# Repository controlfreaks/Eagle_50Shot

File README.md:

# Eagle_50Shot
50 shot klunker's EagleCad files

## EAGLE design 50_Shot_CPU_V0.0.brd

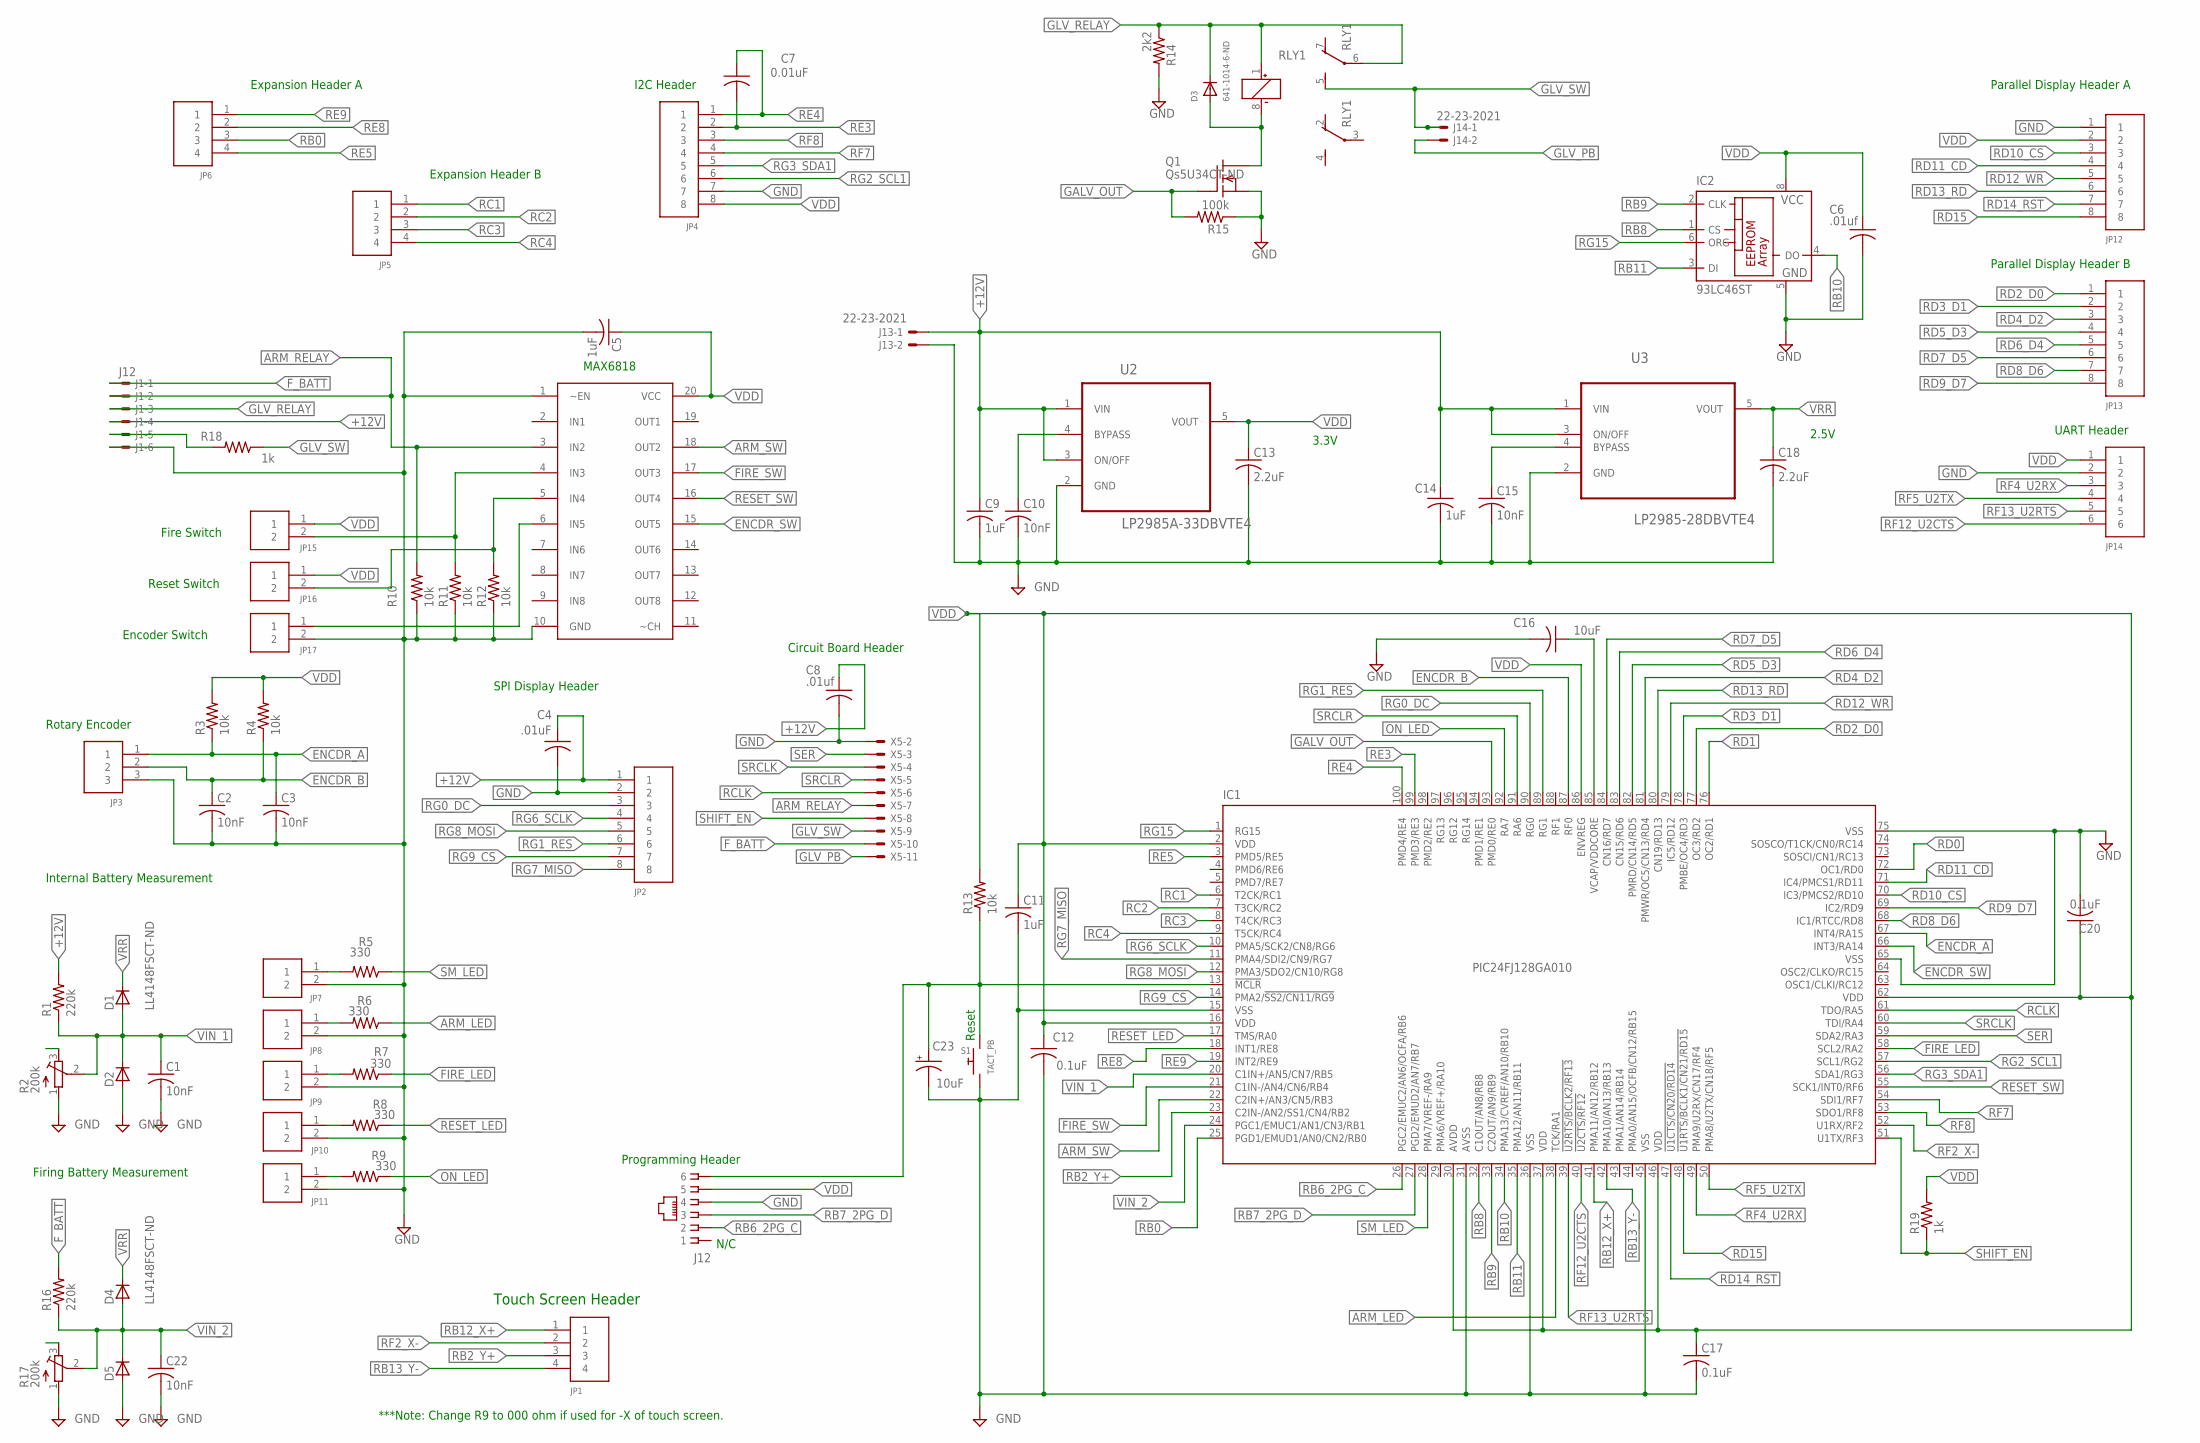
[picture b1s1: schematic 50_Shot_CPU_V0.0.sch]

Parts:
C1, C2, C3, C10, C15, C22: 10nF; C0805
C4: .01uF; C0805
C5, C9, C11, C14: 1uF; C0805
C6, C8: .01uf; C0805
C7: 0.01uF; C0805
C12, C17, C20: 0.1uF; C0805
C13, C18: 2.2uF; C0805
C16: 10uF; C0805
C23: 10uF; CAP3X3
D1, D2, D4, D5: LL4148FSCT-ND; SOD80
D3: 641-1014-6-ND; SOD-123
IC1: PIC24FJ128GA010; TQFP100-14X14
IC2: 93LC46ST; TSSOP8
J1: J12; 22-23-2061
J12: A311422_nd; RJ11-NO_SHIELD
J13, J14: 22-23-2021
JP1, JP5, JP6: SHERLOCK_4PIN_RGT
JP2, JP4, JP12, JP13: SHERLOCK_8PIN_RGT; SHERLOCK_8PIN-RGT
JP3: SHERLOCK_3PIN_RGT
JP7, JP8, JP9, JP10, JP11, JP15, JP16, JP17: SHERLOCK_2PIN_RGT
JP14: SHERLOCK_6PIN_RGT
Q1: Qs5U34CT-ND; SOT23-5L
R1, R16: 220k; M0805
R2, R17: 200k; RTRIM3224X
R3, R4, R10, R11, R12, R13: 10k; M0805
R5, R6, R7, R8, R9: 330; M0805
R14: 2k2; M0805
R15: 100k; M0805
R18, R19: 1k; M0805
RLY1: OMRON; OMRONG6S
S1: TACT_PB; PUSHBUTTON_SMD_SJ
U1: MAX6818; SSOP20
U2: LP2985A-33DBVTE4; SOT95P280X145-5N
U3: LP2985-28DBVTE4; SOT95P280X145-5N
X5: 22-23-2111

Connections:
+12V: C4.1, C8.1, C9.1, C14.1, J1.4, J13.1, JP2.1, R1.2, U2.1 (VIN), U2.3 (ON/OFF), U3.1 (VIN), U3.3 (ON/OFF)
ARM_LED: IC1.38 (TCK/RA1), R6.1
ARM_RELAY: J1.2, R10.2, U1.3 (IN2), X5.7
ARM_SW: IC1.22 (C2IN+/AN3/CN5/RB3), U1.18 (OUT2)
ENCDR_A: C3.1, IC1.67 (INT4/RA15), JP3.1, R3.1
ENCDR_B: C2.1, IC1.87 (RF0), JP3.2, R4.1
ENCDR_SW: IC1.66 (INT3/RA14), U1.15 (OUT5)
FIRE_LED: IC1.58 (SCL2/RA2), R7.1
FIRE_SW: IC1.21 (C1IN-/AN4/CN6/RB4), U1.17 (OUT3)
F_BATT: J1.1, R16.2, X5.10
GALV_OUT: IC1.93 (PMD0/RE0), Q1.1 (G), R15.2
GLV_PB: J14.2, X5.11
GLV_RELAY: D3.C, J1.3, R14.1, RLY1.1 (+), RLY1.6
GLV_SW: J14.1, R18.1, RLY1.5 (S), X5.9
GND: C1.2, C2.2, C3.2, C4.2, C5.2, C6.2, C8.2, C9.2, C10.2, C11.2, C12.2, C13.2, C14.2, C15.2, C16.2, C17.2, C18.2, C20.2, C22.2, C23.-, D2.2 (A), D5.2 (A), IC1.15 (VSS), IC1.31 (AVSS), IC1.36 (VSS), IC1.45 (VSS), IC1.65 (VSS), IC1.75 (VSS), IC2.5 (GND), J1.6, J12.4, J13.2, JP2.2, JP3.3, JP4.7, JP7.2, JP8.2, JP9.2, JP10.2, JP11.2, JP12.1, JP14.2, JP17.2, Q1.2 (S), R2.1 (A), R10.1, R11.1, R12.1, R14.2, R15.1, R17.1 (A), S1.1, S1.2 (1), U1.1 (~EN), U1.10 (GND), U2.2 (GND), U3.2 (GND), X5.2
MCLR: C23.+, IC1.13 (!MCLR), J12.6, R13.1, S1.3 (2), S1.4 (2)
unnamed: D3.A, Q1.5 (D), RLY1.8 (-)
unnamed: JP7.1, R5.2
unnamed: C10.1, U2.4 (BYPASS)
unnamed: C16.1, IC1.85 (VCAP/VDDCORE)
unnamed: JP8.1, R6.2
unnamed: JP17.1, U1.6 (IN5)
unnamed: JP16.2, R12.2, U1.5 (IN4)
unnamed: JP9.1, R7.2
unnamed: J1.5, R18.2
unnamed: JP10.1, R8.2
unnamed: JP11.1, R9.2
unnamed: C15.1, U3.4 (BYPASS)
unnamed: JP15.2, R11.2, U1.4 (IN3)
ON_LED: IC1.92 (RA7), R9.1
RB0: IC1.25 (PGD1/EMUD1/AN0/CN2/RB0), JP6.3
RB2_Y+: IC1.23 (C2IN-/AN2/SS1/CN4/RB2), JP1.3
RB6_2PG_C: IC1.26 (PGC2/EMUC2/AN6/OCFA/RB6), J12.2
RB7_2PG_D: IC1.27 (PGD2/EMUD2/AN7/RB7), J12.3
RB8: IC1.32 (C1OUT/AN8/RB8), IC2.1 (CS)
RB9: IC1.33 (C2OUT/AN9/RB9), IC2.2 (CLK)
RB10: IC1.34 (PMA13/CVREF/AN10/RB10), IC2.4 (DO)
RB11: IC1.35 (PMA12/AN11/RB11), IC2.3 (DI)
RB12_X+: IC1.41 (PMA11/AN12/RB12), JP1.1
RB13_Y-: IC1.42 (PMA10/AN13/RB13), JP1.4
RC1: IC1.6 (T2CK/RC1), JP5.1
RC2: IC1.7 (T3CK/RC2), JP5.2
RC3: IC1.8 (T4CK/RC3), JP5.3
RC4: IC1.9 (T5CK/RC4), JP5.4
RCLK: IC1.61 (TDO/RA5), X5.6
RD0: IC1.72 (OC1/RD0)
RD1: IC1.76 (OC2/RD1)
RD2_D0: IC1.77 (OC3/RD2), JP13.1
RD3_D1: IC1.78 (PMBE/OC4/RD3), JP13.2
RD4_D2: IC1.81 (PMWR/OC5/CN13/RD4), JP13.3
RD5_D3: IC1.82 (PMRD/CN14/RD5), JP13.4
RD6_D4: IC1.83 (CN15/RD6), JP13.5
RD7_D5: IC1.84 (CN16/RD7), JP13.6
RD8_D6: IC1.68 (IC1/RTCC/RD8), JP13.7
RD9_D7: IC1.69 (IC2/RD9), JP13.8
RD10_CS: IC1.70 (IC3/PMCS2/RD10), JP12.3
RD11_CD: IC1.71 (IC4/PMCS1/RD11), JP12.4
RD12_WR: IC1.79 (IC5/RD12), JP12.5
RD13_RD: IC1.80 (CN19/RD13), JP12.6
RD14_RST: IC1.47 (!U1CTS/CN20/RD14), JP12.7
RD15: IC1.48 (!U1RTS/BCLK1/CN21/RD15), JP12.8
RE3: C7.2, IC1.99 (PMD3/RE3), JP4.2
RE4: C7.1, IC1.100 (PMD4/RE4), JP4.1
RE5: IC1.3 (PMD5/RE5), JP6.4
RE8: IC1.18 (INT1/RE8), JP6.2
RE9: IC1.19 (INT2/RE9), JP6.1
RESET_LED: IC1.17 (TMS/RA0), R8.1
RESET_SW: IC1.55 (SCK1/INT0/RF6), U1.16 (OUT4)
RF2_X-: IC1.52 (U1RX/RF2), JP1.2
RF4_U2RX: IC1.49 (PMA9/U2RX/CN17/RF4), JP14.3
RF5_U2TX: IC1.50 (PMA8/U2TX/CN18/RF5), JP14.4
RF7: IC1.54 (SDI1/RF7), JP4.4
RF8: IC1.53 (SDO1/RF8), JP4.3
RF12_U2CTS: IC1.40 (!U2CTS/RF12), JP14.6
RF13_U2RTS: IC1.39 (!U2RTS/BCLK2/RF13), JP14.5
RG0_DC: IC1.90 (RG0), JP2.3
RG1_RES: IC1.89 (RG1), JP2.6
RG2_SCL1: IC1.57 (SCL1/RG2), JP4.6
RG3_SDA1: IC1.56 (SDA1/RG3), JP4.5
RG6_SCLK: IC1.10 (PMA5/SCK2/CN8/RG6), JP2.4
RG7_MISO: IC1.11 (PMA4/SDI2/CN9/RG7), JP2.8
RG8_MOSI: IC1.12 (PMA3/SDO2/CN10/RG8), JP2.5
RG9_CS: IC1.14 (PMA2/!SS2/CN11/RG9), JP2.7
RG15: IC1.1 (RG15), IC2.6 (ORG)
SER: IC1.59 (SDA2/RA3), X5.3
SHIFT_EN: IC1.51 (U1TX/RF3), R19.1, X5.8
SM_LED: IC1.28 (PMA7/VREF-/RA9), R5.1
SRCLK: IC1.60 (TDI/RA4), X5.4
SRCLR: IC1.91 (RA6), X5.5
VDD: C5.1, C6.1, C11.1, C12.1, C13.1, C17.1, C20.1, IC1.2 (VDD), IC1.16 (VDD), IC1.30 (AVDD), IC1.37 (VDD), IC1.46 (VDD), IC1.62 (VDD), IC1.86 (ENVREG), IC2.8 (VCC), J12.5, JP4.8, JP12.2, JP14.1, JP15.1, JP16.1, R3.2, R4.2, R13.2, R19.2, U1.20 (VCC), U2.5 (VOUT)
VIN_1: C1.1, D1.2 (A), D2.1 (C), IC1.20 (C1IN+/AN5/CN7/RB5), R1.1, R2.2 (S)
VIN_2: C22.1, D4.2 (A), D5.1 (C), IC1.24 (PGC1/EMUC1/AN1/CN3/RB1), R16.1, R17.2 (S)
VRR: C18.1, D1.1 (C), D4.1 (C), U3.5 (VOUT)

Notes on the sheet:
3.3V
Reset
2.5V
Internal Battery Measurement
SPI Display Header
N/C
Expansion Header A
Programming Header
MAX6818
Circuit Board Header
I2C Header
Fire Switch
Reset Switch
Encoder Switch
Firing Battery Measurement
***Note: Change R9 to 000 ohm if used for -X of touch screen.
Touch Screen Header
Rotary Encoder
Expansion Header B
Parallel Display Header A
Parallel Display Header B
UART Header

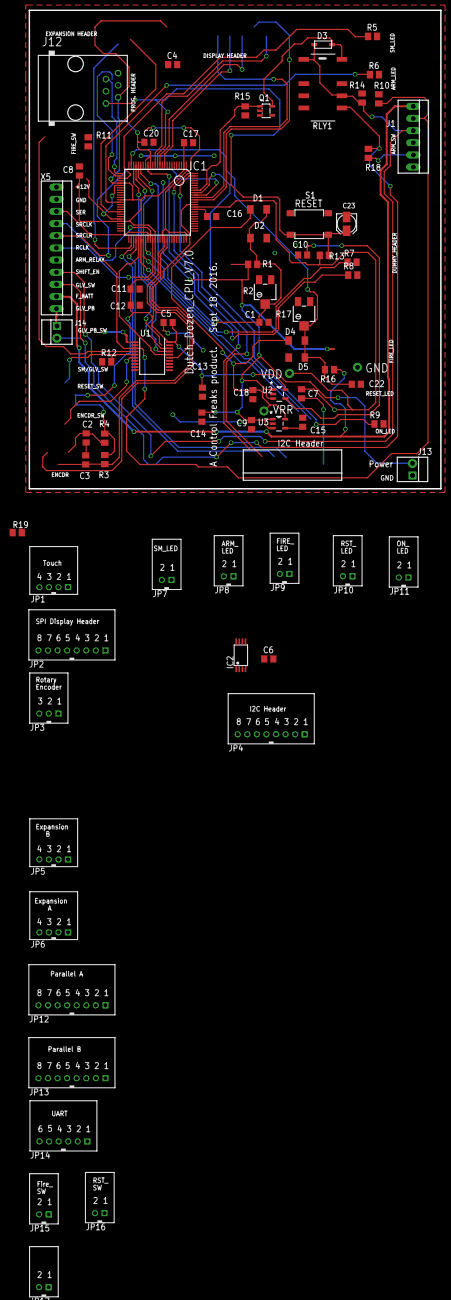
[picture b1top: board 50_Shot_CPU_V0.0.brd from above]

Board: 2 copper layers, 86.0 x 100.0 mm, 75 parts (0 on the bottom side), 91 nets.

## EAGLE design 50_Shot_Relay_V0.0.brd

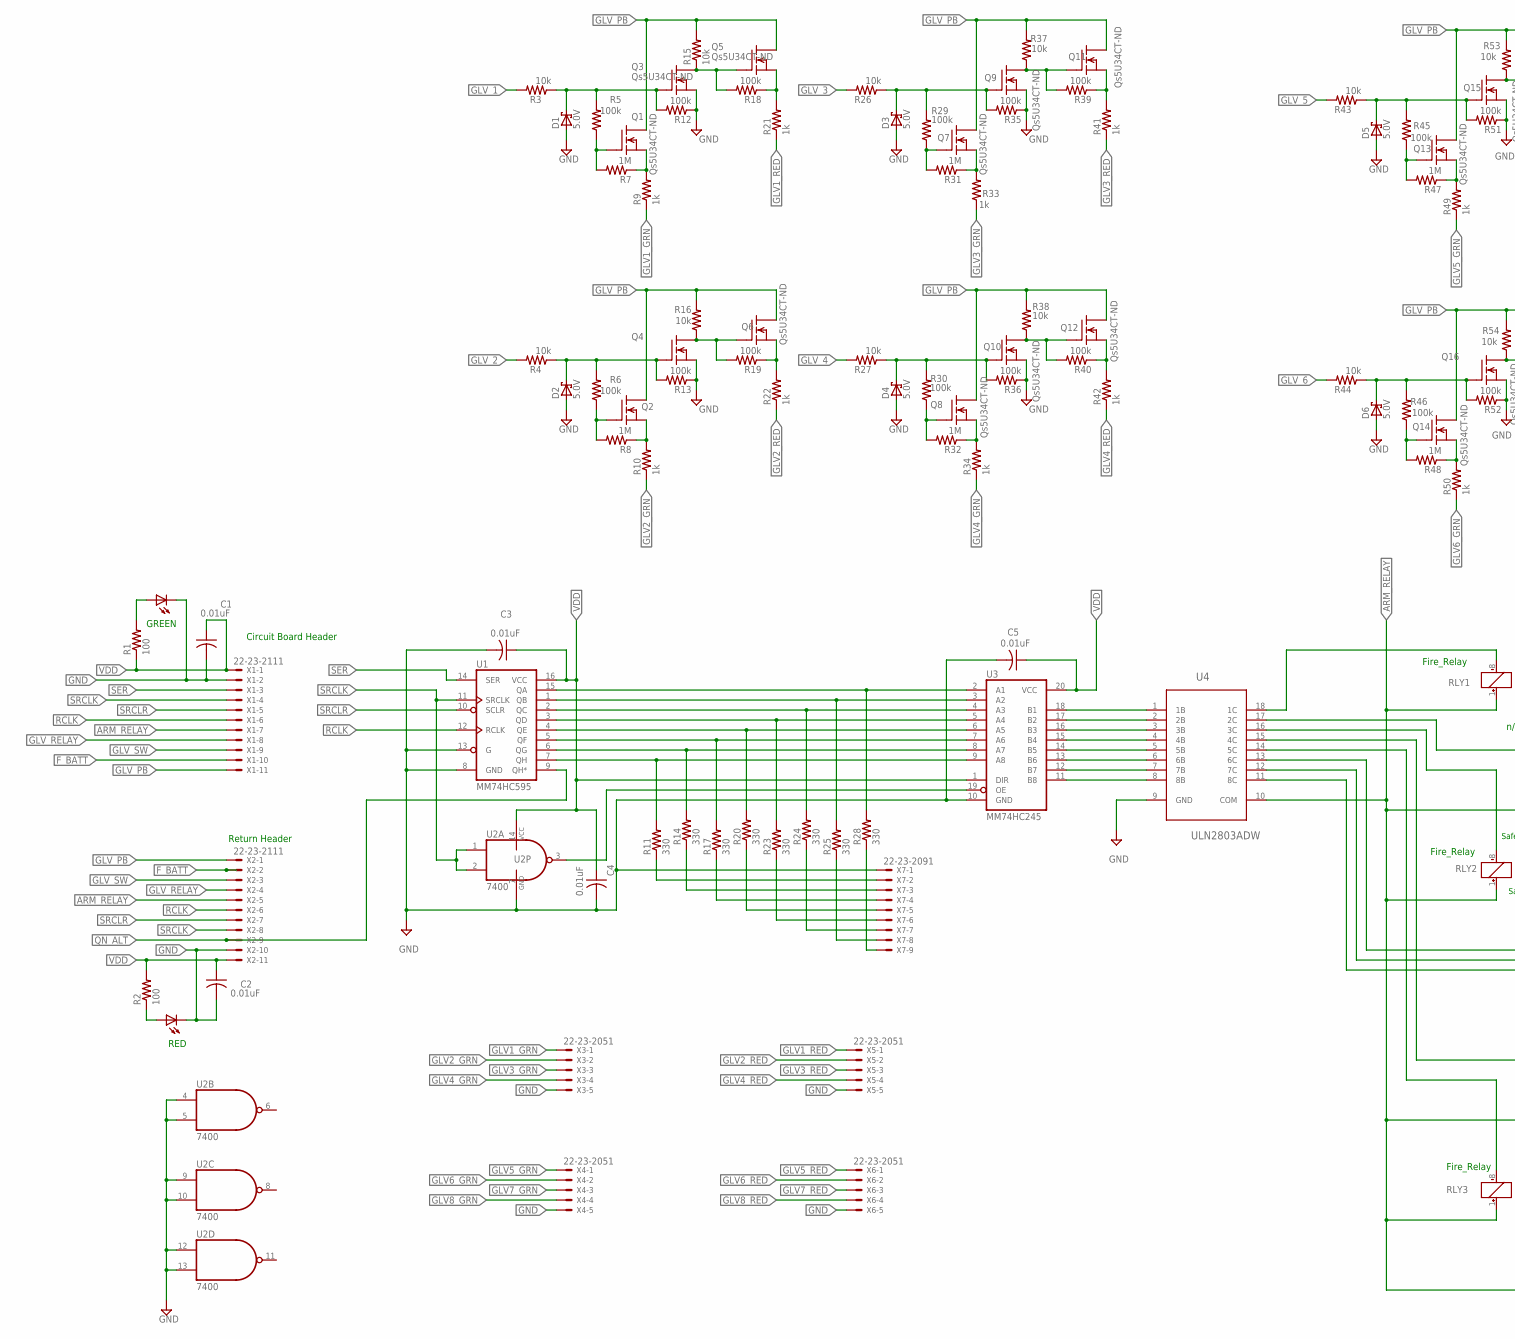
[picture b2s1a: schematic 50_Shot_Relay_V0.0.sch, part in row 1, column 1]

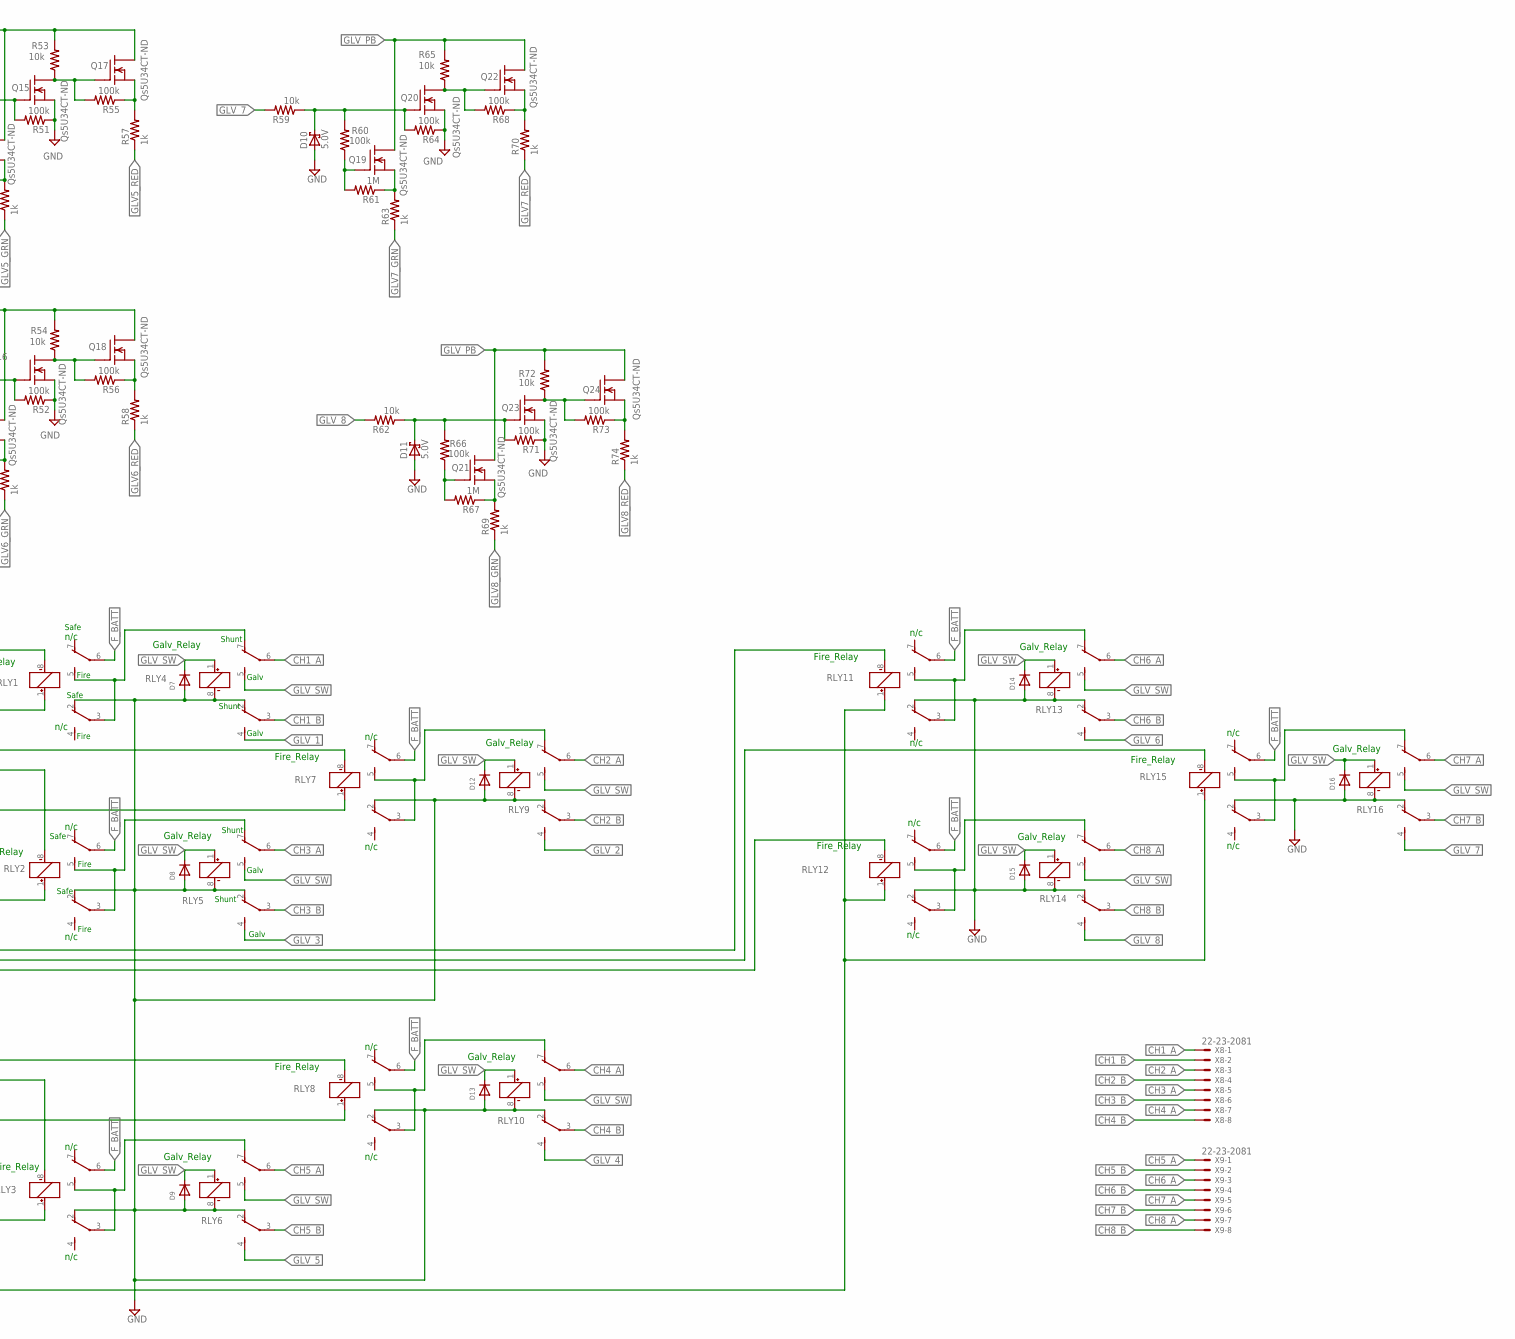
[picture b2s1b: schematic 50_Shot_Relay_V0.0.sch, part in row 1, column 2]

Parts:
C1, C2: 0.01uF; C0805; MPN VY2103M63Y5US63V7
C3, C4, C5: 0.01uF; C0805
D1, D2, D3, D4, D5, D6, D10, D11: 5.0V; SOT23
D7, D8, D9, D12, D13, D14, D15, D16: SA2M-E3/5ATGICT-ND; DO214AC
LED1, LED2: LEDCHIP-LED0805; CHIP-LED0805
Q1, Q2, Q3, Q4, Q5, Q6, Q7, Q8, Q9, Q10, Q11, Q12, Q13, Q14, Q15, Q16, Q17, Q18, Q19, Q20, Q21, Q22, Q23, Q24: Qs5U34CT-ND; SOT23-5L
R1, R2: 100; M0805
R3, R4, R15, R16, R26, R27, R37, R38, R43, R44, R53, R54, R59, R62, R65, R72: 10k; M0805
R5, R6, R12, R13, R18, R19, R29, R30, R35, R36, R39, R40, R45, R46, R51, R52, R55, R56, R60, R64, R66, R68, R71, R73: 100k; M0805
R7, R8, R31, R32, R47, R48, R61, R67: 1M; M0805
R9, R10, R21, R22, R33, R34, R41, R42, R49, R50, R57, R58, R63, R69, R70, R74: 1k; M0805
R11, R14, R17, R20, R23, R24, R25, R28: 330; M0805
RLY1, RLY2, RLY3, RLY4, RLY5, RLY6, RLY7, RLY8, RLY9, RLY10, RLY11, RLY12, RLY13, RLY14, RLY15, RLY16: OMRON; OMRONG6S
U1: MM74HC595; TSSOP16
U2: 7400; TSSOP14
U3: MM74HC245; TSSOP20
U4: ULN2803ADW; SOIC127P1030X265-18N
X1, X2: 22-23-2111
X3, X4, X5, X6: 22-23-2051
X7: 22-23-2091
X8, X9: 22-23-2081

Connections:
ARM_RELAY: RLY1.1 (+), RLY2.1 (+), RLY3.1 (+), RLY7.1 (+), RLY8.1 (+), RLY11.1 (+), RLY12.1 (+), RLY15.1 (+), U4.10 (COM), X1.7, X2.5
CH1_A: RLY4.6, X8.1
CH1_B: RLY4.3, X8.2
CH2_A: RLY9.6, X8.3
CH2_B: RLY9.3, X8.4
CH3_A: RLY5.6, X8.5
CH3_B: RLY5.3, X8.6
CH4_A: RLY10.6, X8.7
CH4_B: RLY10.3, X8.8
CH5_A: RLY6.6, X9.1
CH5_B: RLY6.3, X9.2
CH6_A: RLY13.6, X9.3
CH6_B: RLY13.3, X9.4
CH7_A: RLY16.6, X9.5
CH7_B: RLY16.3, X9.6
CH8_A: RLY14.6, X9.7
CH8_B: RLY14.3, X9.8
F_BATT: RLY1.6, RLY2.6, RLY3.6, RLY7.6, RLY8.6, RLY11.6, RLY12.6, RLY15.6, X1.10, X2.2
GLV1_GRN: R9.1, X3.1
GLV1_RED: R21.1, X5.1
GLV2_GRN: R10.1, X3.2
GLV2_RED: R22.1, X5.2
GLV3_GRN: R33.1, X3.3
GLV3_RED: R41.1, X5.3
GLV4_GRN: R34.1, X3.4
GLV4_RED: R42.1, X5.4
GLV5_GRN: R49.1, X4.1
GLV5_RED: R57.1, X6.1
GLV6_GRN: R50.1, X4.2
GLV6_RED: R58.1, X6.2
GLV7_GRN: R63.1, X4.3
GLV7_RED: R70.1, X6.3
GLV8_GRN: R69.1, X4.4
GLV8_RED: R74.1, X6.4
GLV_1: R3.2, RLY4.4 (S)
GLV_2: R4.2, RLY9.4 (S)
GLV_3: R26.2, RLY5.4 (S)
GLV_4: R27.2, RLY10.4 (S)
GLV_5: R43.2, RLY6.4 (S)
GLV_6: R44.2, RLY13.4 (S)
GLV_7: R59.2, RLY16.4 (S)
GLV_8: R62.2, RLY14.4 (S)
GLV_PB: Q1.5 (D), Q2.5 (D), Q5.5 (D), Q6.5 (D), Q7.5 (D), Q8.5 (D), Q11.5 (D), Q12.5 (D), Q13.5 (D), Q14.5 (D), Q17.5 (D), Q18.5 (D), Q19.5 (D), Q21.5 (D), Q22.5 (D), Q24.5 (D), R15.2, R16.2, R37.2, R38.2, R53.2, R54.2, R65.2, R72.2, X1.11, X2.1
GLV_RELAY: X1.8, X2.4
GLV_SW: D7.C, D8.C, D9.C, D12.C, D13.C, D14.C, D15.C, D16.C, RLY4.1 (+), RLY4.5 (S), RLY5.1 (+), RLY5.5 (S), RLY6.1 (+), RLY6.5 (S), RLY9.1 (+), RLY9.5 (S), RLY10.1 (+), RLY10.5 (S), RLY13.1 (+), RLY13.5 (S), RLY14.1 (+), RLY14.5 (S), RLY16.1 (+), RLY16.5 (S), X1.9, X2.3
GND: C1.2, C2.2, C3.2, C4.2, C5.2, D1.1 (A), D2.1 (A), D3.1 (A), D4.1 (A), D5.1 (A), D6.1 (A), D7.A, D8.A, D9.A, D10.1 (A), D11.1 (A), D12.A, D13.A, D14.A, D15.A, D16.A, LED1.C, LED2.C, Q3.2 (S), Q4.2 (S), Q9.2 (S), Q10.2 (S), Q15.2 (S), Q16.2 (S), Q20.2 (S), Q23.2 (S), R12.1, R13.1, R35.1, R36.1, R51.1, R52.1, R64.1, R71.1, RLY1.2 (O), RLY2.2 (O), RLY3.2 (O), RLY4.2 (O), RLY4.8 (-), RLY5.2 (O), RLY5.8 (-), RLY6.2 (O), RLY6.8 (-), RLY7.2 (O), RLY8.2 (O), RLY9.2 (O), RLY9.8 (-), RLY10.2 (O), RLY10.8 (-), RLY11.2 (O), RLY12.2 (O), RLY13.2 (O), RLY13.8 (-), RLY14.2 (O), RLY14.8 (-), RLY15.2 (O), RLY16.2 (O), RLY16.8 (-), U1.8 (GND), U1.13 (G), U2.4 (I0), U2.5 (I1), U2.7 (GND), U2.9 (I0), U2.10 (I1), U2.12 (I0), U2.13 (I1), U3.10 (GND), U4.9 (GND), X1.2, X2.10, X3.5, X4.5, X5.5, X6.5, X7.1
unnamed: LED2.A, R2.1
unnamed: R17.1, X7.4
unnamed: R14.1, X7.3
unnamed: LED1.A, R1.2
unnamed: R11.1, X7.2
unnamed: RLY1.3, RLY1.5 (S), RLY4.7 (O)
unnamed: R28.2, U1.15 (QA), U3.2 (A1)
unnamed: R25.2, U1.1 (QB), U3.3 (A2)
unnamed: R24.2, U1.2 (QC), U3.4 (A3)
unnamed: R23.2, U1.3 (QD), U3.5 (A4)
unnamed: R20.2, U1.4 (QE), U3.6 (A5)
unnamed: R17.2, U1.5 (QF), U3.7 (A6)
unnamed: R14.2, U1.6 (QG), U3.8 (A7)
unnamed: R11.2, U1.7 (QH), U3.9 (A8)
unnamed: U3.18 (B1), U4.1 (1B)
unnamed: U2.3 (O), U3.19 (OE)
unnamed: U3.17 (B2), U4.2 (2B)
unnamed: U3.16 (B3), U4.3 (3B)
unnamed: U3.15 (B4), U4.4 (4B)
unnamed: U3.14 (B5), U4.5 (5B)
unnamed: U3.13 (B6), U4.6 (6B)
unnamed: U3.12 (B7), U4.7 (7B)
unnamed: U3.11 (B8), U4.8 (8B)
unnamed: RLY1.8 (-), U4.18 (1C)
unnamed: RLY7.8 (-), U4.17 (2C)
unnamed: RLY2.8 (-), U4.16 (3C)
unnamed: RLY8.8 (-), U4.15 (4C)
unnamed: RLY3.8 (-), U4.14 (5C)
unnamed: RLY11.8 (-), U4.13 (6C)
unnamed: RLY15.8 (-), U4.12 (7C)
unnamed: RLY12.8 (-), U4.11 (8C)
unnamed: RLY2.3, RLY2.5 (S), RLY5.7 (O)
unnamed: RLY7.3, RLY7.5 (S), RLY9.7 (O)
unnamed: RLY3.3, RLY3.5 (S), RLY6.7 (O)
unnamed: RLY8.3, RLY8.5 (S), RLY10.7 (O)
unnamed: RLY11.3, RLY11.5 (S), RLY13.7 (O)
unnamed: RLY12.3, RLY12.5 (S), RLY14.7 (O)
unnamed: RLY15.3, RLY15.5 (S), RLY16.7 (O)
unnamed: D1.3 (C), Q3.1 (G), R3.1, R5.2, R12.2
unnamed: Q1.1 (G), R5.1, R7.2
unnamed: Q5.2 (S), R18.1, R21.2
unnamed: Q1.2 (S), R7.1, R9.2
unnamed: Q3.5 (D), Q5.1 (G), R15.1, R18.2
unnamed: D2.3 (C), Q4.1 (G), R4.1, R6.2, R13.2
unnamed: Q2.1 (G), R6.1, R8.2
unnamed: Q2.2 (S), R8.1, R10.2
unnamed: Q4.5 (D), Q6.1 (G), R16.1, R19.2
unnamed: Q6.2 (S), R19.1, R22.2
unnamed: D3.3 (C), Q9.1 (G), R26.1, R29.2, R35.2
unnamed: Q7.1 (G), R29.1, R31.2
unnamed: Q7.2 (S), R31.1, R33.2
unnamed: Q9.5 (D), Q11.1 (G), R37.1, R39.2
unnamed: Q11.2 (S), R39.1, R41.2
unnamed: D4.3 (C), Q10.1 (G), R27.1, R30.2, R36.2
unnamed: Q8.1 (G), R30.1, R32.2
unnamed: Q8.2 (S), R32.1, R34.2
unnamed: Q10.5 (D), Q12.1 (G), R38.1, R40.2
unnamed: Q12.2 (S), R40.1, R42.2
unnamed: D10.3 (C), Q20.1 (G), R59.1, R60.2, R64.2
unnamed: Q19.1 (G), R60.1, R61.2
unnamed: Q19.2 (S), R61.1, R63.2
unnamed: Q20.5 (D), Q22.1 (G), R65.1, R68.2
unnamed: Q22.2 (S), R68.1, R70.2
unnamed: D6.3 (C), Q16.1 (G), R44.1, R46.2, R52.2
unnamed: Q14.1 (G), R46.1, R48.2
unnamed: Q14.2 (S), R48.1, R50.2
unnamed: Q16.5 (D), Q18.1 (G), R54.1, R56.2
unnamed: Q18.2 (S), R56.1, R58.2
unnamed: D5.3 (C), Q15.1 (G), R43.1, R45.2, R51.2
unnamed: Q13.1 (G), R45.1, R47.2
unnamed: Q13.2 (S), R47.1, R49.2
unnamed: Q15.5 (D), Q17.1 (G), R53.1, R55.2
unnamed: Q17.2 (S), R55.1, R57.2
unnamed: D11.3 (C), Q23.1 (G), R62.1, R66.2, R71.2
unnamed: Q21.1 (G), R66.1, R67.2
unnamed: Q21.2 (S), R67.1, R69.2
unnamed: Q23.5 (D), Q24.1 (G), R72.1, R73.2
unnamed: Q24.2 (S), R73.1, R74.2
unnamed: R28.1, X7.9
unnamed: R25.1, X7.8
unnamed: R24.1, X7.7
unnamed: R23.1, X7.6
unnamed: R20.1, X7.5
QN_ALT: U1.9 (QH*), X2.9
RCLK: U1.12 (RCLK), X1.6, X2.6
SER: U1.14 (SER), X1.3
SRCLK: U1.11 (SRCLK), U2.1 (I0), U2.2 (I1), X1.4, X2.8
SRCLR: U1.10 (SCLR), X1.5, X2.7
VDD: C1.1, C2.1, C3.1, C4.1, C5.1, R1.1, R2.2, U1.16 (VCC), U2.14 (VCC), U3.1 (DIR), U3.20 (VCC), X1.1, X2.11

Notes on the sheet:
Fire_Relay
Galv_Relay
n/c
Safe
Fire
Shunt
Galv
Circuit Board Header
Return Header
RED
GREEN

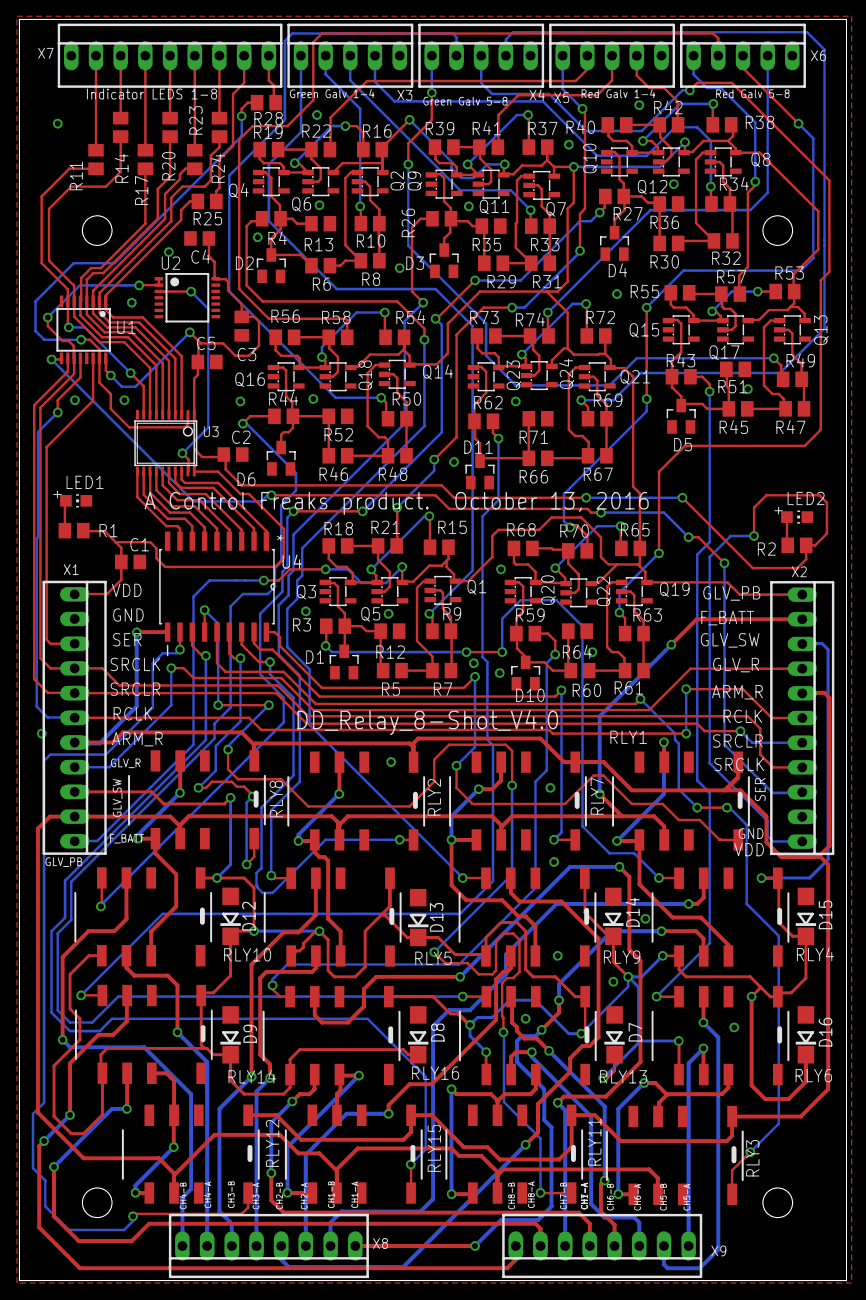
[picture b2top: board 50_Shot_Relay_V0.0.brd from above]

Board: 2 copper layers, 85.1 x 129.7 mm, 150 parts (0 on the bottom side), 135 nets.

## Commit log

2020-02-11 testing push/pull
2020-02-11 trying this again
2020-02-12 add relay board
2020-02-12 add relay board again
2020-02-12 add proper relay board
2020-02-13 removed SM switch (RB2)
2020-02-13 converted SPI display header
2020-02-13 converted rotary encoder header
2020-02-13 converted programming header
2020-02-13 converted LED headers
2020-02-13 Added EEPROM to schematic
2020-02-13 Removed 5V reg and parts
2020-02-13 Added parallel display header
2020-02-13 Added UART Header
2020-02-13 Added fire/reset/encoder switches
